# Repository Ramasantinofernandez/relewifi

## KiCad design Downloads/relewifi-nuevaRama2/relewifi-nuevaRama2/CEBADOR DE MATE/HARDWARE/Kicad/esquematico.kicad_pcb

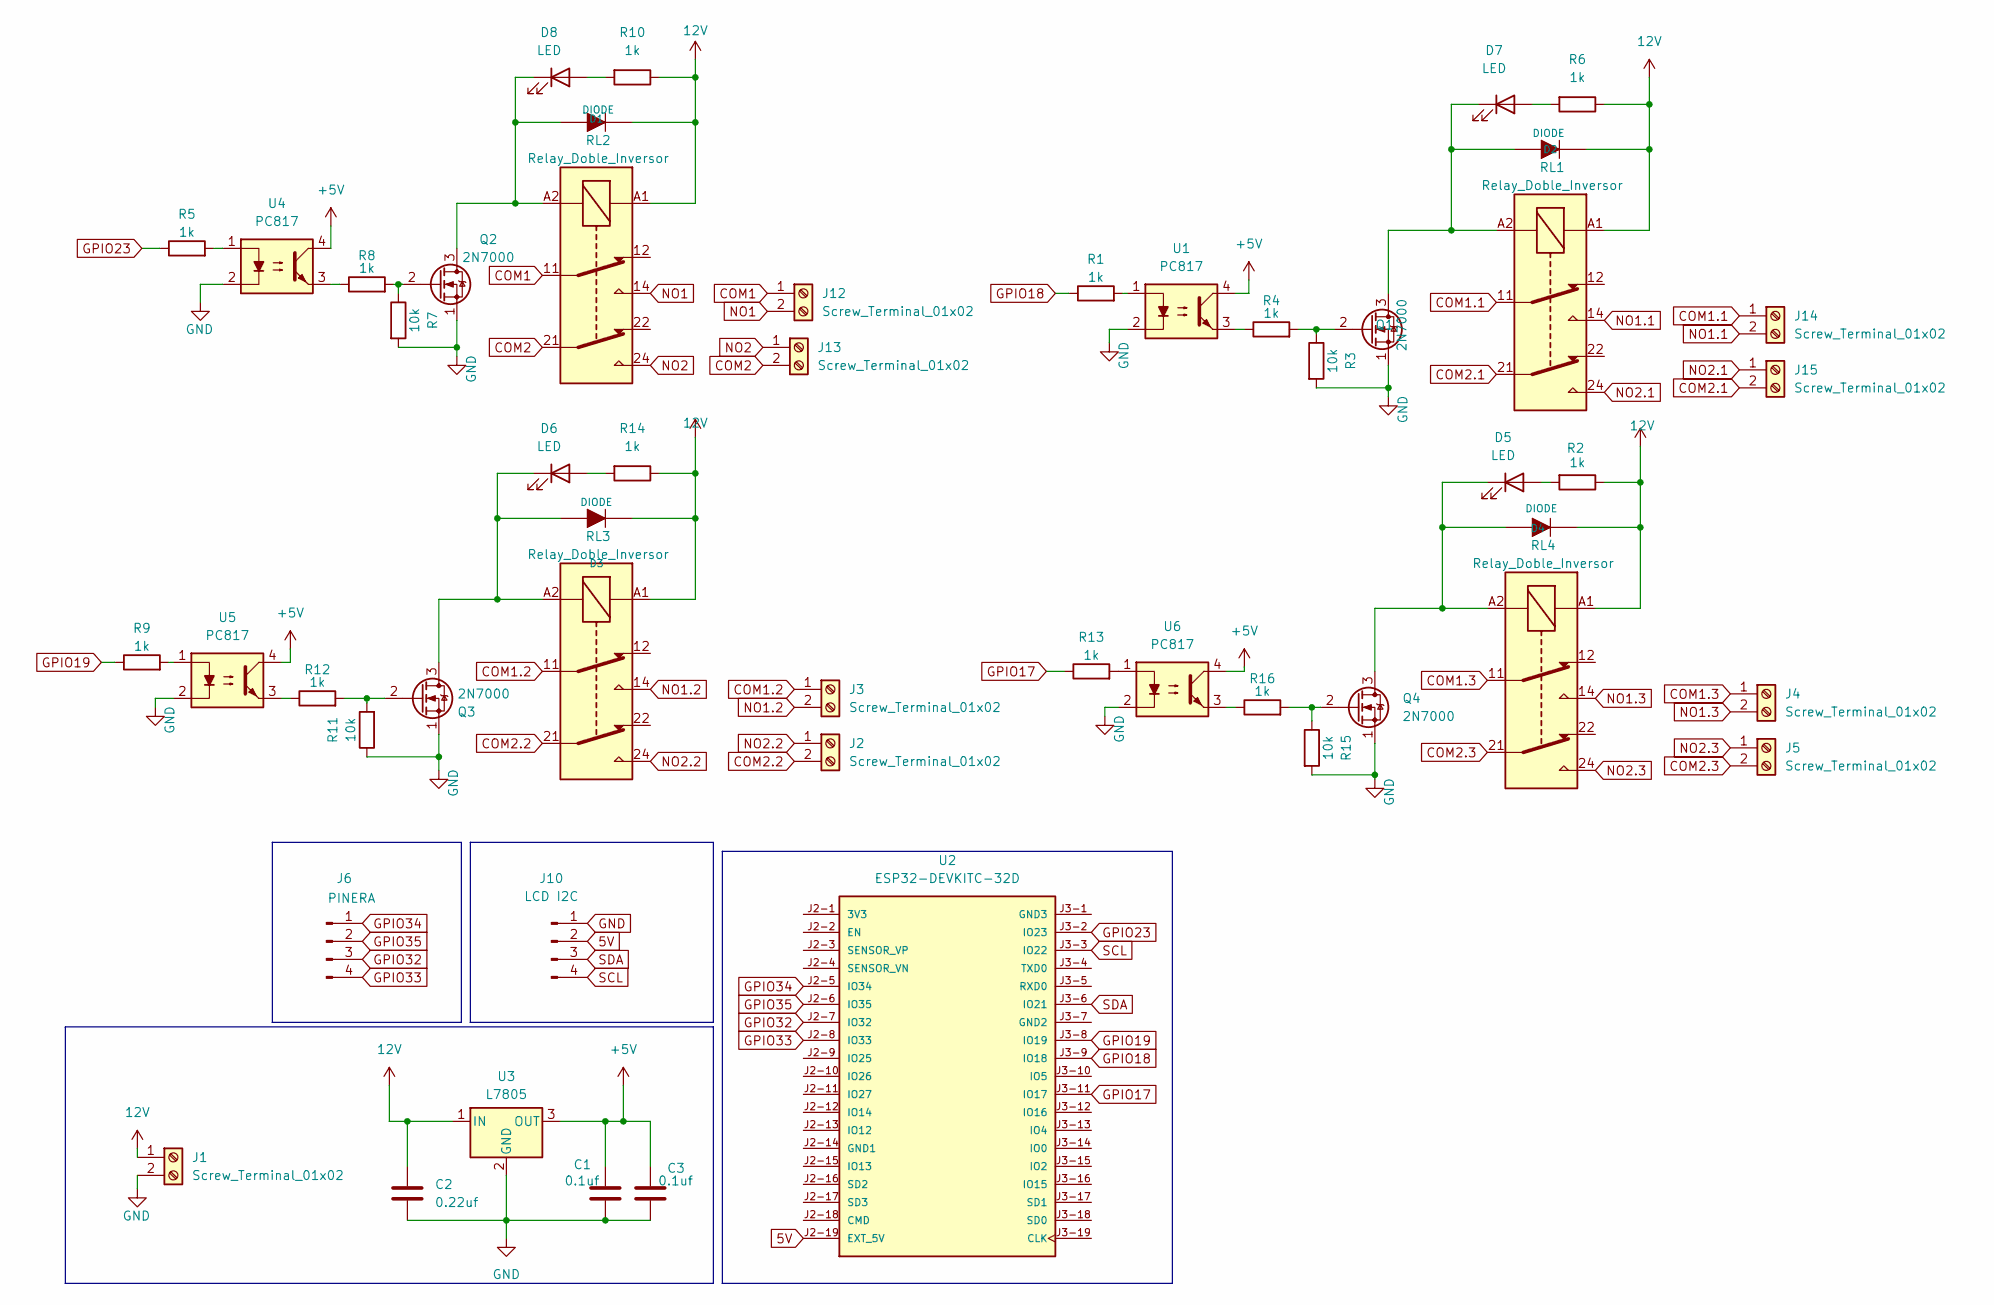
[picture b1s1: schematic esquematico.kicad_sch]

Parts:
C1, C3: 0.1uf; C_0805_2012Metric_Pad1.18x1.45mm_HandSolder
C2: 0.22uf; C_0805_2012Metric_Pad1.18x1.45mm_HandSolder
D1, D2, D3, D4: DIODE; D_SMA
D5, D6, D7, D8: LED; LED_D5.0mm
J1, J2, J3, J4, J5, J12, J13, J14, J15: Screw_Terminal_01x02; TerminalBlock_bornier-2_P5.08mm
J6: PINERA; PinHeader_1x04_P2.54mm_Vertical
J10: LCD I2C; pin_strip_4
Q1, Q2, Q3, Q4: 2N7000; to92
R1, R2, R4, R5, R6, R8, R9, R10, R12, R13, R14, R16: 1k; R_0805_2012Metric
R3, R7, R11, R15: 10k; R_0805_2012Metric
RL1, RL2, RL3, RL4: Relay_Doble_Inversor; Relay_DPDT_Schrack-RT2-FormC_RM5mm
U1, U4, U5, U6: PC817; SSO-4_6.7x5.1mm_P2.54mm_Clearance8mm
U2: ESP32-DEVKITC-32D; MODULE_ESP32-DEVKITC-32D; PARTREV V4
U3: L7805; TO-263-3_TabPin2

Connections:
5V: J10.2, U2.J2-19 (EXT_5V)
12V: C2.1, D1.2 (K), D2.2 (K), D3.2 (K), D4.2 (K), J1.1, R2.1, R6.1, R10.1, R14.1, RL1.A1, RL2.A1, RL3.A1, RL4.A1, U3.1 (IN)
+5V: C1.1, C3.1, U1.4, U3.3 (OUT), U4.4, U5.4, U6.4
COM1: J12.1, RL2.11
COM1.1: J14.1, RL1.11
COM1.2: J3.1, RL3.11
COM1.3: J4.1, RL4.11
COM2: J13.2, RL2.21
COM2.1: J15.2, RL1.21
COM2.2: J2.2, RL3.21
COM2.3: J5.2, RL4.21
GND: C1.2, C2.2, C3.2, J1.2, J10.1, Q1.1 (S), Q2.1 (S), Q3.1 (S), Q4.1 (S), R3.2, R7.2, R11.1, R15.2, U1.2, U3.2 (GND), U4.2, U5.2, U6.2
GPIO17: R13.1, U2.J3-11 (IO17)
GPIO18: R1.1, U2.J3-9 (IO18)
GPIO19: R9.1, U2.J3-8 (IO19)
GPIO23: R5.1, U2.J3-2 (IO23)
GPIO32: J6.3, U2.J2-7 (IO32)
GPIO33: J6.4, U2.J2-8 (IO33)
GPIO34: J6.1, U2.J2-5 (IO34)
GPIO35: J6.2, U2.J2-6 (IO35)
NO1: J12.2, RL2.14
NO1.1: J14.2, RL1.14
NO1.2: J3.2, RL3.14
NO1.3: J4.2, RL4.14
NO2: J13.1, RL2.24
NO2.1: J15.1, RL1.24
NO2.2: J2.1, RL3.24
NO2.3: J5.1, RL4.24
unnamed: D1.1 (A), D8.1 (K), Q2.3 (D), RL2.A2
unnamed: D2.1 (A), D7.1 (K), Q1.3 (D), RL1.A2
unnamed: D3.1 (A), D6.1 (K), Q3.3 (D), RL3.A2
unnamed: D4.1 (A), D5.1 (K), Q4.3 (D), RL4.A2
unnamed: D5.2 (A), R2.2
unnamed: D6.2 (A), R14.2
unnamed: D7.2 (A), R6.2
unnamed: D8.2 (A), R10.2
unnamed: Q1.2 (G), R3.1, R4.2
unnamed: Q2.2 (G), R7.1, R8.2
unnamed: Q3.2 (G), R11.2, R12.2
unnamed: Q4.2 (G), R15.1, R16.2
unnamed: R1.2, U1.1
unnamed: R4.1, U1.3
unnamed: R5.2, U4.1
unnamed: R8.1, U4.3
unnamed: R9.2, U5.1
unnamed: R12.1, U5.3
unnamed: R13.2, U6.1
unnamed: R16.1, U6.3
SCL: J10.4, U2.J3-3 (IO22)
SDA: J10.3, U2.J3-6 (IO21)

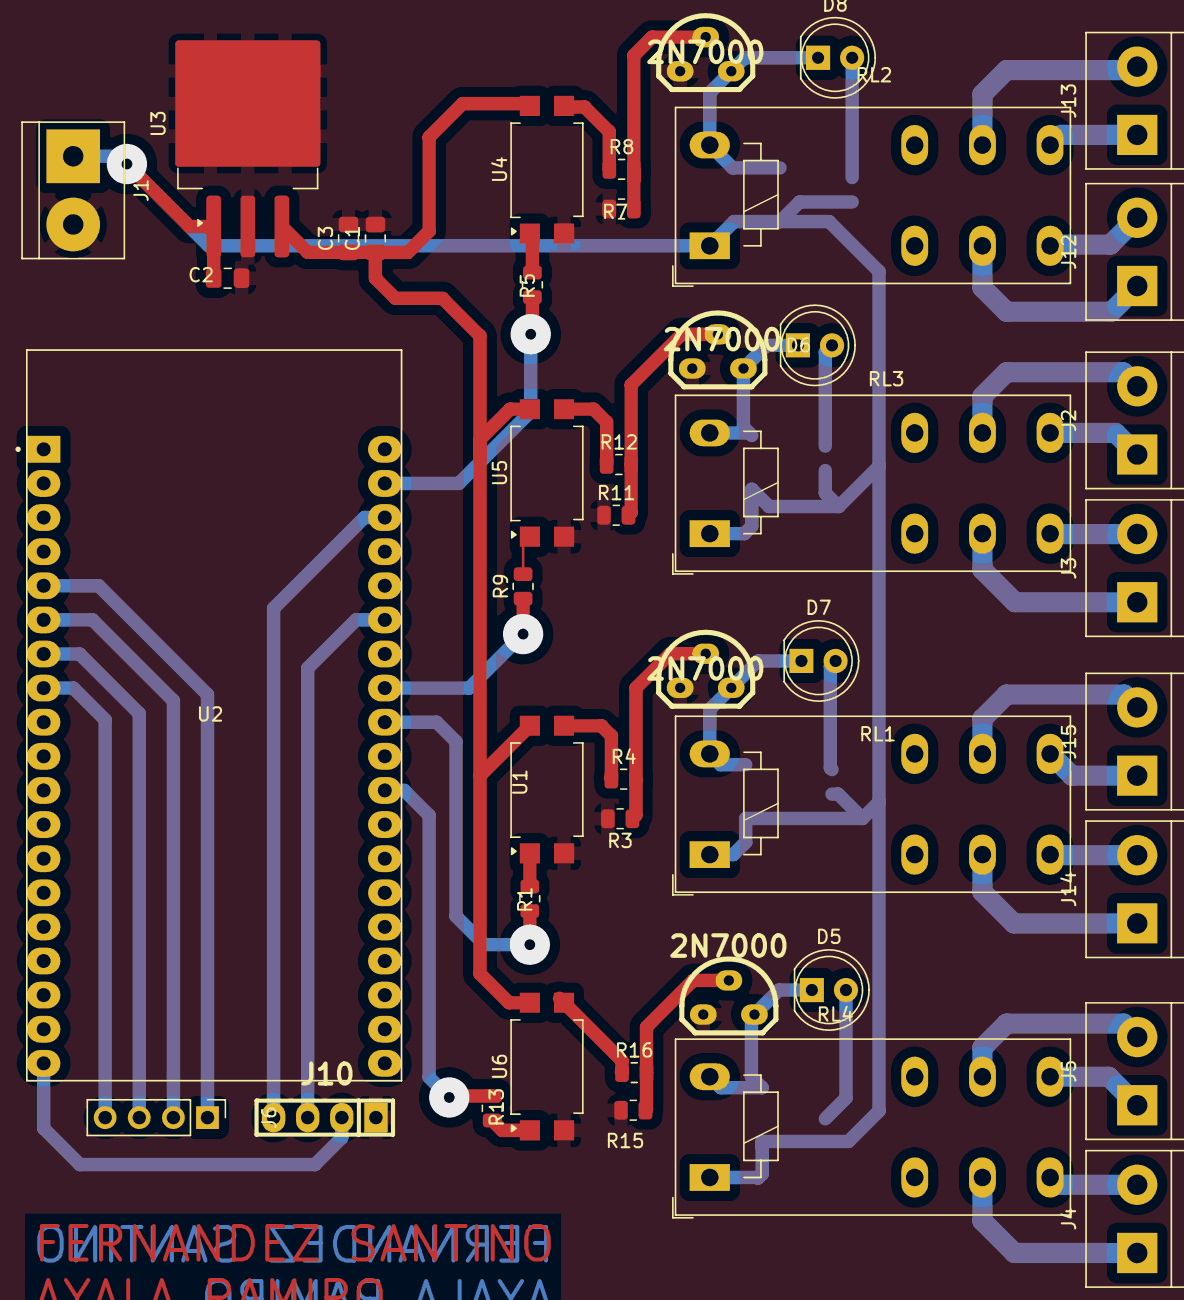
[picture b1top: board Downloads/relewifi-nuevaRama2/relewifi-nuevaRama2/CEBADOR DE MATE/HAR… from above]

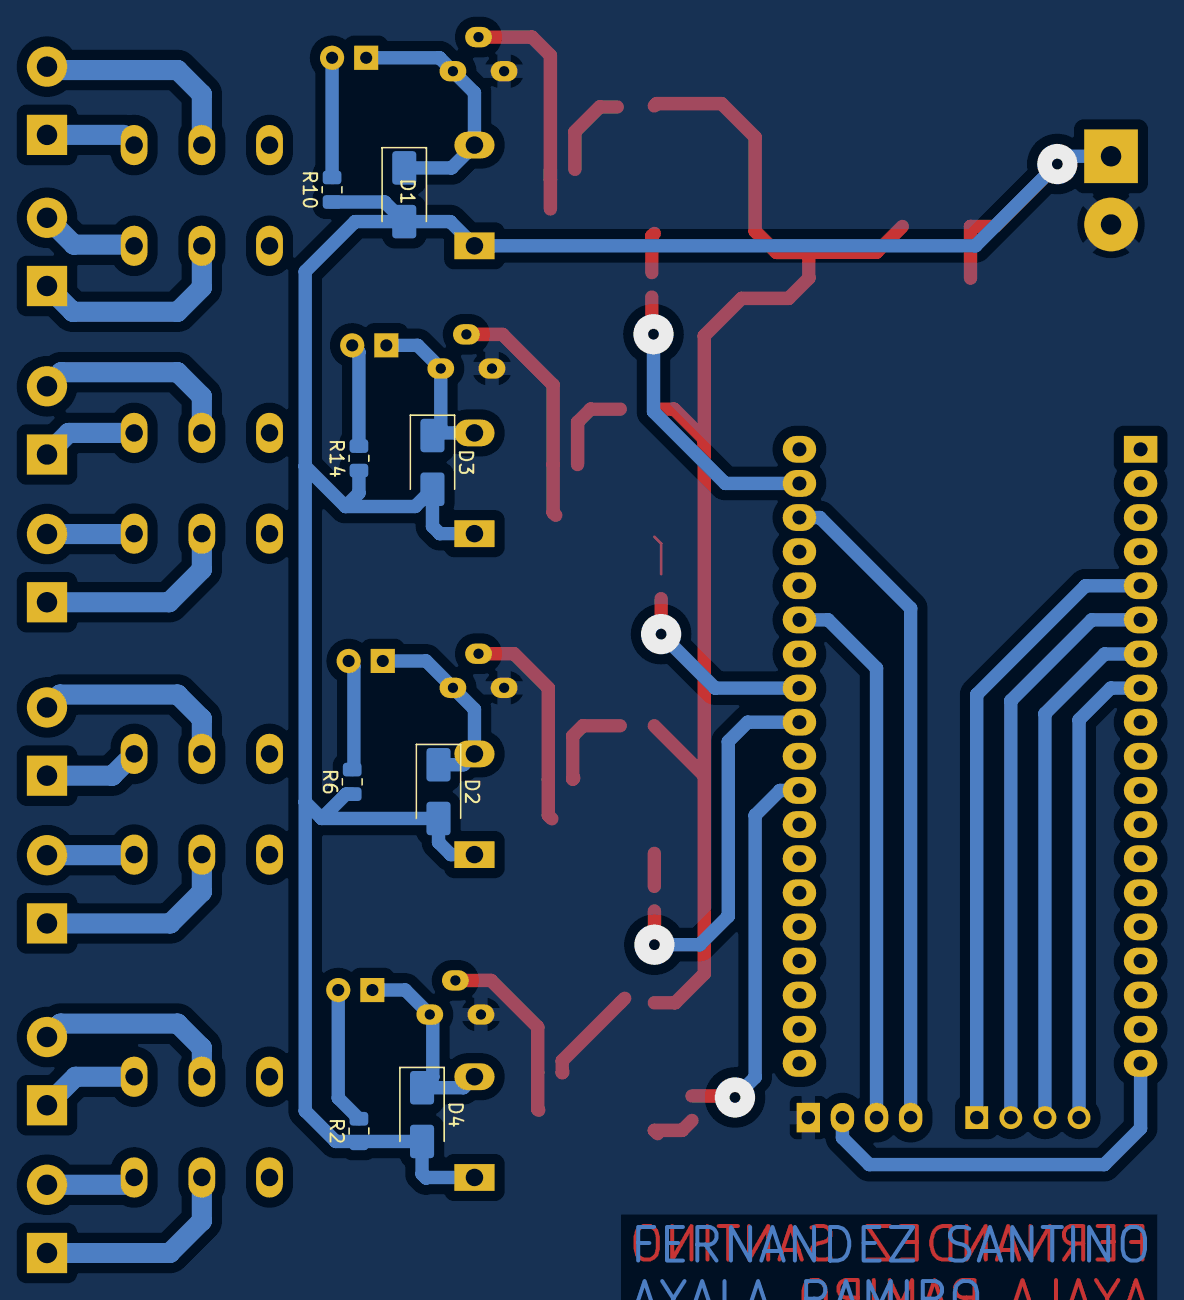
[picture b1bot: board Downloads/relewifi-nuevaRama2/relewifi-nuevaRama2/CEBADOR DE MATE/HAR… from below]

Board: 2 copper layers, 52 parts (8 on the bottom side), 50 nets.

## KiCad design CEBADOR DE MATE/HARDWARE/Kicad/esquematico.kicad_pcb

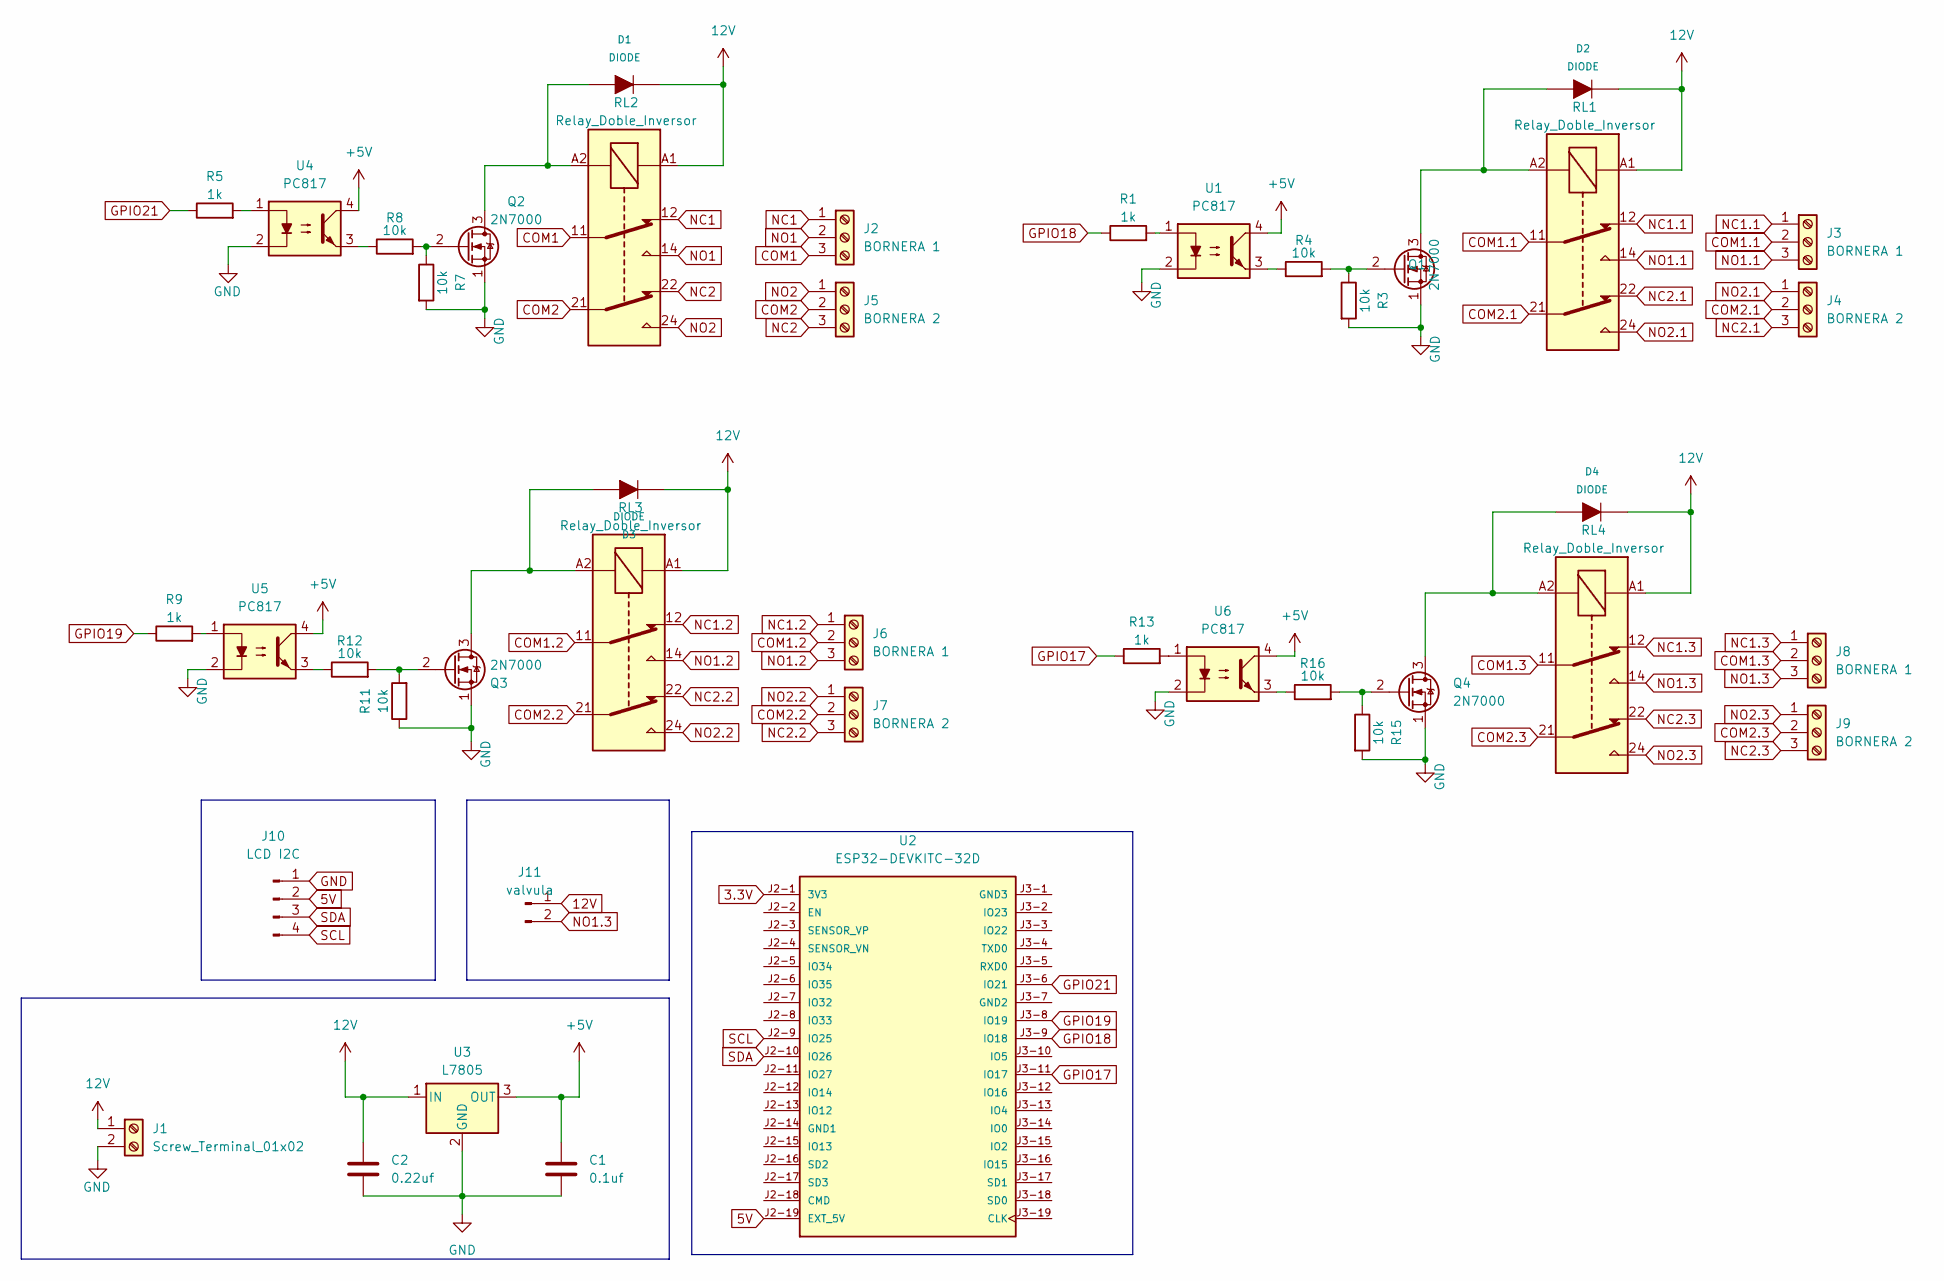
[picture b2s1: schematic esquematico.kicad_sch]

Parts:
C1: 0.1uf; C_0805_2012Metric_Pad1.18x1.45mm_HandSolder
C2: 0.22uf; C_0805_2012Metric_Pad1.18x1.45mm_HandSolder
D1, D2, D3, D4: DIODE; D_SMA
J1: Screw_Terminal_01x02; TerminalBlock_bornier-2_P5.08mm
J2, J3, J6, J8: BORNERA 1; TerminalBlock_bornier-3_P5.08mm
J4, J5, J7, J9: BORNERA 2; TerminalBlock_bornier-3_P5.08mm
J10: LCD I2C; pin_strip_4
J11: valvula; PinHeader_1x02_P2.54mm_Vertical
Q1, Q2, Q3, Q4: 2N7000; to92
R1, R5, R9, R13: 1k; R_0805_2012Metric
R3, R4, R7, R8, R11, R12, R15, R16: 10k; R_0805_2012Metric
RL1, RL2, RL3, RL4: Relay_Doble_Inversor; Relay_DPDT_Schrack-RT2-FormC_RM5mm
U1, U4, U5, U6: PC817; SSO-4_6.7x5.1mm_P2.54mm_Clearance8mm
U2: ESP32-DEVKITC-32D; MODULE_ESP32-DEVKITC-32D; PARTREV V4
U3: L7805; TO-220-3_Vertical

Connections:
3.3V: U2.J2-1 (3V3)
5V: J10.2, U2.J2-19 (EXT_5V)
12V: C2.1, D1.2 (K), D2.2 (K), D3.2 (K), D4.2 (K), J1.1, J11.1, RL1.A1, RL2.A1, RL3.A1, RL4.A1, U3.1 (IN)
+5V: C1.1, U1.4, U3.3 (OUT), U4.4, U5.4, U6.4
COM1: J2.3, RL2.11
COM1.1: J3.2, RL1.11
COM1.2: J6.2, RL3.11
COM1.3: J8.2, RL4.11
COM2: J5.2, RL2.21
COM2.1: J4.2, RL1.21
COM2.2: J7.2, RL3.21
COM2.3: J9.2, RL4.21
GND: C1.2, C2.2, J1.2, J10.1, Q1.1 (S), Q2.1 (S), Q3.1 (S), Q4.1 (S), R3.2, R7.2, R11.1, R15.2, U1.2, U3.2 (GND), U4.2, U5.2, U6.2
GPIO17: R13.1, U2.J3-11 (IO17)
GPIO18: R1.1, U2.J3-9 (IO18)
GPIO19: R9.1, U2.J3-8 (IO19)
GPIO21: R5.1, U2.J3-6 (IO21)
NC1: J2.1, RL2.12
NC1.1: J3.1, RL1.12
NC1.2: J6.1, RL3.12
NC1.3: J8.1, RL4.12
NC2: J5.3, RL2.22
NC2.1: J4.3, RL1.22
NC2.2: J7.3, RL3.22
NC2.3: J9.3, RL4.22
NO1: J2.2, RL2.14
NO1.1: J3.3, RL1.14
NO1.2: J6.3, RL3.14
NO1.3: J8.3, J11.2, RL4.14
NO2: J5.1, RL2.24
NO2.1: J4.1, RL1.24
NO2.2: J7.1, RL3.24
NO2.3: J9.1, RL4.24
unnamed: D1.1 (A), Q2.3 (D), RL2.A2
unnamed: D2.1 (A), Q1.3 (D), RL1.A2
unnamed: D3.1 (A), Q3.3 (D), RL3.A2
unnamed: D4.1 (A), Q4.3 (D), RL4.A2
unnamed: Q1.2 (G), R3.1, R4.2
unnamed: Q2.2 (G), R7.1, R8.2
unnamed: Q3.2 (G), R11.2, R12.2
unnamed: Q4.2 (G), R15.1, R16.2
unnamed: R1.2, U1.1
unnamed: R4.1, U1.3
unnamed: R5.2, U4.1
unnamed: R8.1, U4.3
unnamed: R9.2, U5.1
unnamed: R12.1, U5.3
unnamed: R13.2, U6.1
unnamed: R16.1, U6.3
SCL: J10.4, U2.J2-9 (IO25)
SDA: J10.3, U2.J2-10 (IO26)

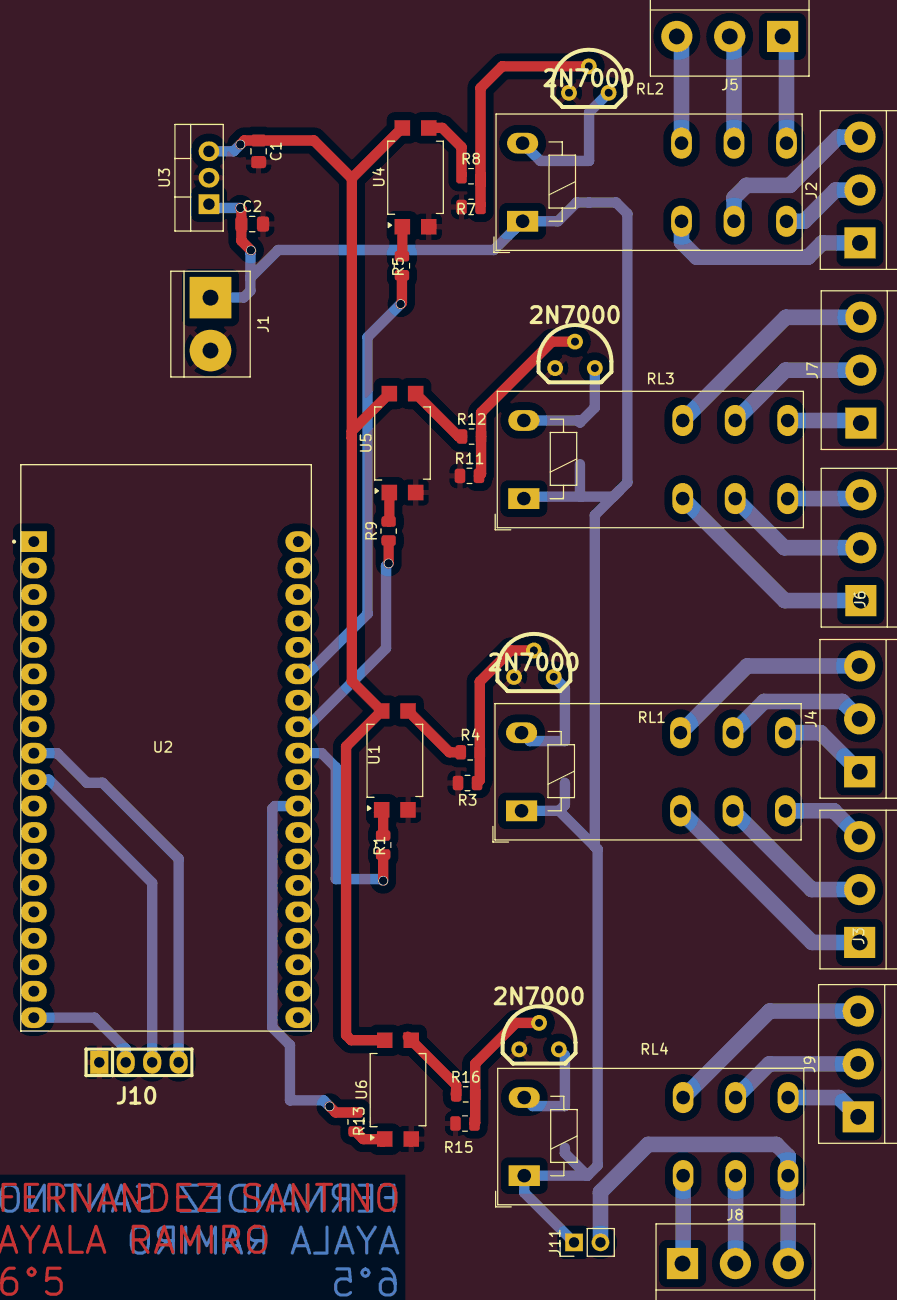
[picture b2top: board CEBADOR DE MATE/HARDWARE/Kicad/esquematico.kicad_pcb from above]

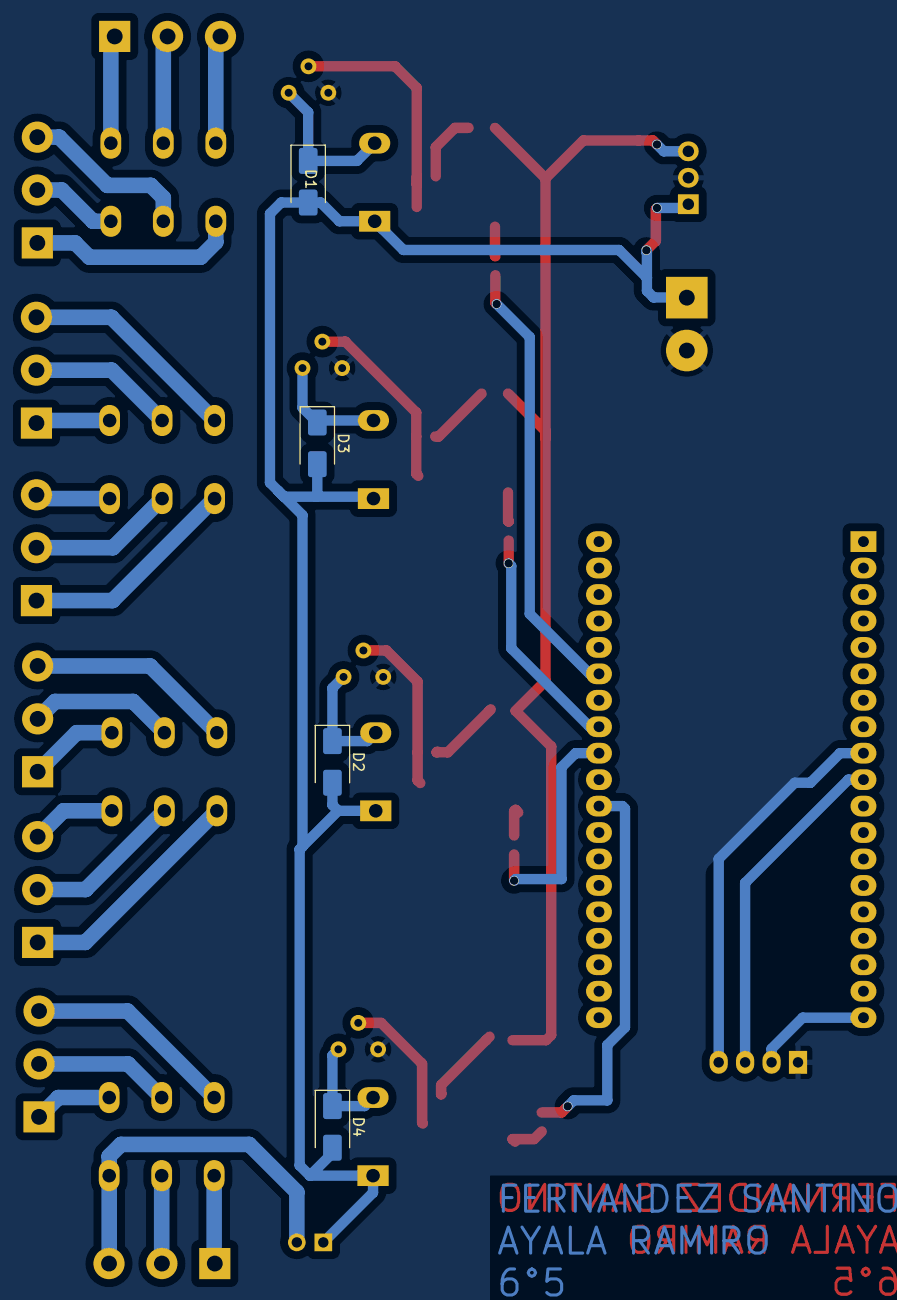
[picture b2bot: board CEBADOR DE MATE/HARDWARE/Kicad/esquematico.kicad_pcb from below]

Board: 2 copper layers, 43 parts (4 on the bottom side), 50 nets.

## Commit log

2025-04-07 esquematico
2025-05-04 se termino el esquematico y falta terminar el pcb
2025-05-08 terminamos el pcb falta ordenar un poco mas
2025-05-08 terminamos el pcb pero falta ordenarlo un poco
2025-05-12 se termino el esquematico y pcb
2025-05-19 se acomodo el pcb y se ordeno el esquematico
2025-06-06 falta acomodar el pcb y achicarlo un poco
2025-06-06 se termino el pcb y ya lo ordene
2025-06-12 termine el pcb y agregue una pinera para sensores,y agrande los pads y vias
2025-06-17 termianmos la placa
2025-06-17 termine el pcb
